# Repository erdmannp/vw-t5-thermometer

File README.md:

# vw-t5-thermometer
Integrates a thermometer (inside and outside) into an old VW T5 dashboard

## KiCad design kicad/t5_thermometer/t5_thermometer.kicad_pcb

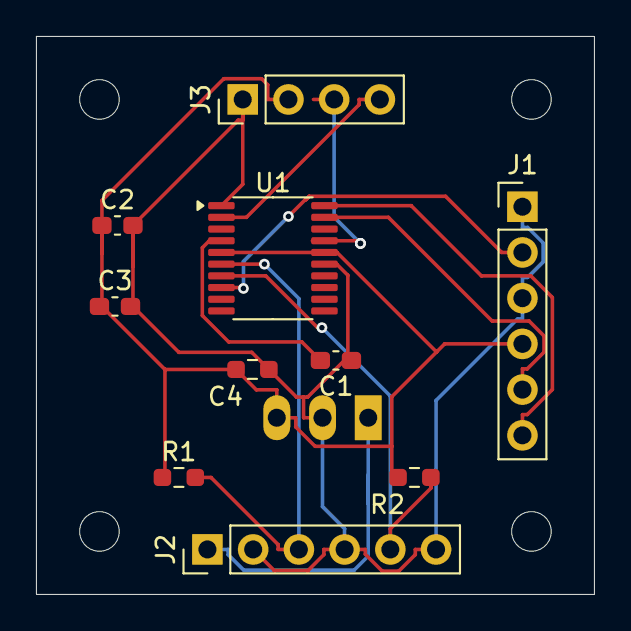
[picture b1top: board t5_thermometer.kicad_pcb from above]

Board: 2 copper layers, 31.0 x 31.0 mm, 15 parts (1 on the bottom side), 11 nets.

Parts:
C1, C2: 100n; C_0603_1608Metric_Pad1.08x0.95mm_HandSolder
C3: 4,7u; C_0603_1608Metric_Pad1.08x0.95mm_HandSolder
C4: 22n; R_0603_1608Metric_Pad0.98x0.95mm_HandSolder
H1, H2, H3, H4: MountingHole_Pad; MountingHole_2.2mm_M2
J1: DBG; PinHeader_1x06_P2.54mm_Vertical
J2: PinHeader_1x06_P2.54mm_Vertical
J3: Display; PinHeader_1x04_P2.54mm_Vertical
R1, R2: R10k; R_0603_1608Metric_Pad0.98x0.95mm_HandSolder
U1: STM32F042F6Px; TSSOP-20_4.4x6.5mm_P0.65mm
U2: TSR_1-2433; Converter_DCDC_TRACO_TSR-1_THT

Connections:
+3.3V: C2.1, C3.1, C4.2, J1.4, J3.2, R1.1, R2.2, U1.5 (VDDA), U1.16 (VDD), U2.3 (Vout)
/ADC_INDOOR: J2.3, R1.2, U1.6 (PA0)
/ADC_OUTDOOR: J2.5, R2.1, U1.7 (PA1)
/I2C_SCL_DISPLAY: J3.3, U1.17 (PA9/PA11)
/I2C_SDA_DISPLAY: J3.4, U1.2 (PF0)
/SYS_SWCLK: J1.6, U1.20 (PA14)
/SYS_SWDIO: J1.5, U1.19 (PA13)
/USART2_TX_DBG: J1.2, U1.8 (PA2)
GND: C1.1, C2.2, C3.2, C4.1, J1.1, J1.3, J2.2, J2.4, J2.6, J3.1, U1.1 (PB8), U1.15 (VSS), U2.2 (GND)
unnamed: J2.1, U2.1 (Vin)
unnamed: C1.2, U1.4 (NRST)

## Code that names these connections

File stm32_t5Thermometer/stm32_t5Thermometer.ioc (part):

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Mcu.Name=STM32F042F6Px
Mcu.Package=TSSOP20
Mcu.UserName=STM32F042F6Px
PA0.GPIOParameters=GPIO_Label
PA0.GPIO_Label=ADC_INDOOR
PA0.Mode=IN0
PA0.Signal=ADC_IN0
PA1.GPIOParameters=GPIO_Label
PA1.GPIO_Label=ADC_OUTDOOR
PA1.Mode=IN1
PA1.Signal=ADC_IN1
PA13.Mode=Serial_Wire
PA13.Signal=SYS_SWDIO
PA14.Mode=Serial_Wire
PA14.Signal=SYS_SWCLK
PA2.GPIOParameters=GPIO_Label
PA2.GPIO_Label=USART2_TX_DBG
PA2.Signal=USART2_TX
PA9.GPIOParameters=GPIO_Label,GPIO_Pu
PA9.GPIO_Label=I2C_SCL_DISPLAY
PA9.GPIO_Pu=GPIO_PULLUP
PA9.Mode=I2C
PA9.Signal=I2C1_SCL
PF0-OSC_IN.GPIOParameters=GPIO_Label,GPIO_Pu
PF0-OSC_IN.GPIO_Label=I2C_SDA_DISPLAY
PF0-OSC_IN.GPIO_Pu=GPIO_PULLUP
PF0-OSC_IN.Mode=I2C
PF0-OSC_IN.Signal=I2C1_SDA
RCC.SYSCLKFreq_VALUE=8000000
board=custom

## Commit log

2024-10-19 Configure all necessary Pins, I2C DMA is missing
2024-10-20 Add 3D Model for VW T5
2024-10-20 Add configuration and PCB design which was ordered.
2024-10-20 Add generated files and ssd1306 HAL submodule
2024-10-20 Add GLCD Font Calculator
2024-10-20 Remove font generator
2024-10-22 Add new 3d model, add font generator and fonts
2024-10-26 schematic change: - Add 4,7k pull up for I2C - Connect PB8 to GND. PB8 was initially planned as I2C SCL, but due to the fact that it also operates as BOOT0 pin, it cannot be pulled up.
2024-10-27 free PB8 pin, fix several issues, add configurability to ssd1306 lib
2024-10-27 Change Layout to match the current working status: BOOT0 is now connected to GND
2024-10-28 Finalizing.
    - Adding DMA and ADC
    - Check temperature every 500 ms.
